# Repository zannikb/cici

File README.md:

# Cici macropad

x18 macropad created by zannikb.

# Photos

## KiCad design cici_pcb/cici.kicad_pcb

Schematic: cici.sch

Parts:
D1, D2, D3, D4, D5, D6, D7, D8, D9, D10, D11, D12, D13, D14, D15, D16, D17, D18: D; D_DO-35_SOD27_P5.08mm_Horizontal
OLED1: OLED; OLED_1side
SW1, SW2, SW3, SW4, SW5, SW6, SW7, SW8, SW9, SW10, SW11, SW12, SW13, SW14, SW15, SW16, SW17, SW18: SW_PUSH; CherryMX_1u
SW_R1: SW_PUSH; ResetSW_1side
U1: ProMicro; ProMicro_v3

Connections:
GND: OLED1.4 (GND), SW_R1.2, U1.3 (GND), U1.4 (GND), U1.23 (GND)
unnamed: D1.2 (A), SW1.2
unnamed: D2.2 (A), SW2.2
unnamed: D3.2 (A), SW3.2
unnamed: D4.2 (A), SW4.2
unnamed: D5.2 (A), SW5.2
unnamed: D6.2 (A), SW6.2
unnamed: D7.2 (A), SW7.2
unnamed: D8.2 (A), SW8.2
unnamed: D9.2 (A), SW9.2
unnamed: D10.2 (A), SW10.2
unnamed: D11.2 (A), SW11.2
unnamed: D12.2 (A), SW12.2
unnamed: D13.2 (A), SW13.2
unnamed: D14.2 (A), SW14.2
unnamed: D15.2 (A), SW15.2
unnamed: D16.2 (A), SW16.2
unnamed: D17.2 (A), SW17.2
unnamed: D18.2 (A), SW18.2
SDA: OLED1.1 (SDA), U1.5 (2/D1/SDA)
SLC: OLED1.2 (SCL), U1.6 (3/D0/SCL)
VCC: OLED1.3 (VCC), U1.21 (VCC)
col0: SW1.1, SW5.1, SW9.1, SW13.1, U1.20 (F4/A3)
col1: SW2.1, SW6.1, SW10.1, SW14.1, SW17.1, U1.19 (F5/A2)
col2: SW3.1, SW7.1, SW11.1, SW15.1, SW18.1, U1.18 (F6/A1)
col3: SW4.1, SW8.1, SW12.1, SW16.1, U1.17 (F7/A0)
col4: U1.16 (B1/15)
col5: U1.15 (B3/14)
data: U1.2 (RX1/D2)
reset: SW_R1.1, U1.22 (RST)
row0: D1.1 (K), D2.1 (K), D3.1 (K), D4.1 (K), U1.7 (4/D4)
row1: D5.1 (K), D6.1 (K), D7.1 (K), D8.1 (K), U1.8 (5/C6)
row2: D9.1 (K), D10.1 (K), D11.1 (K), D12.1 (K), U1.9 (6/D7)
row3: D13.1 (K), D14.1 (K), D15.1 (K), D16.1 (K), U1.10 (7/E6)
row4: D17.1 (K), D18.1 (K), U1.11 (8/B4)

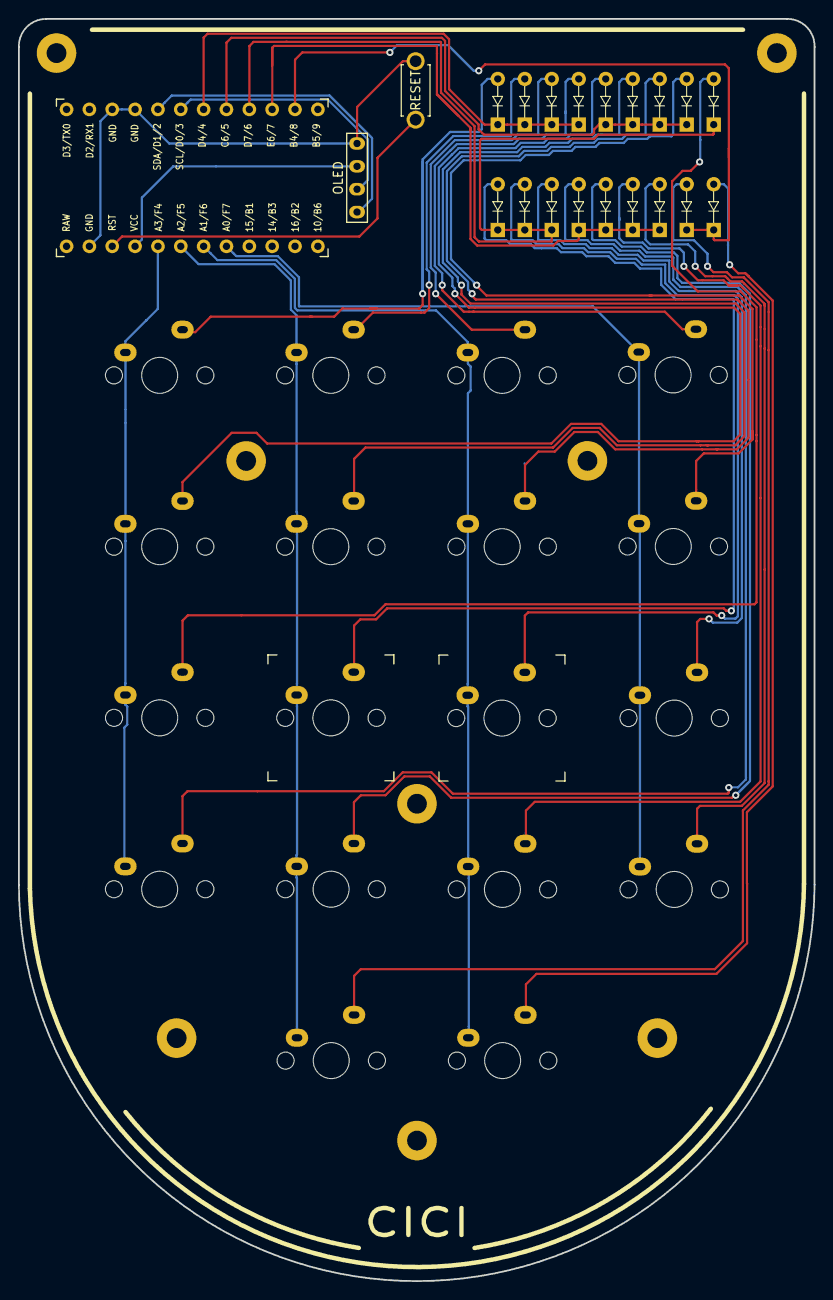
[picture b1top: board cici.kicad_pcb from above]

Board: 2 copper layers, 88.4 x 140.3 mm, 39 parts (0 on the bottom side), 32 nets.

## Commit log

2022-04-13 aggiunto bottom
2022-04-13 realizzato bottom e sistemato fori per viti
2022-04-15 creazione pezzo acrilico e sistemazione fori
2022-04-15 pulizia
2022-04-17 creazione gerber e conclusione primo tentativo
2022-04-29 prima versione conclusa. inizio seconda
2022-04-29 cambio immagine
2022-04-29 clean
2022-04-30 aggiornamento pcb
